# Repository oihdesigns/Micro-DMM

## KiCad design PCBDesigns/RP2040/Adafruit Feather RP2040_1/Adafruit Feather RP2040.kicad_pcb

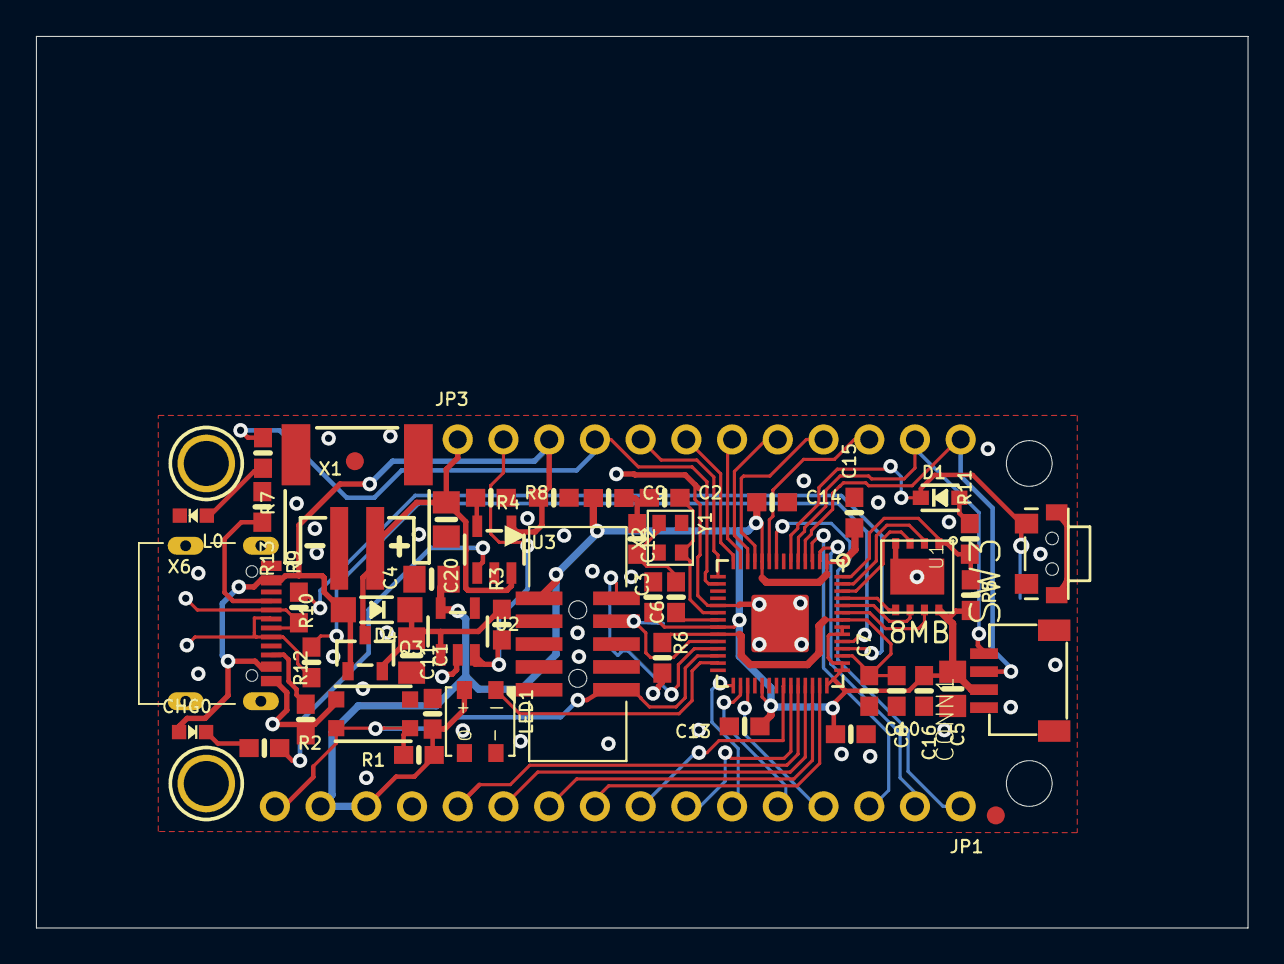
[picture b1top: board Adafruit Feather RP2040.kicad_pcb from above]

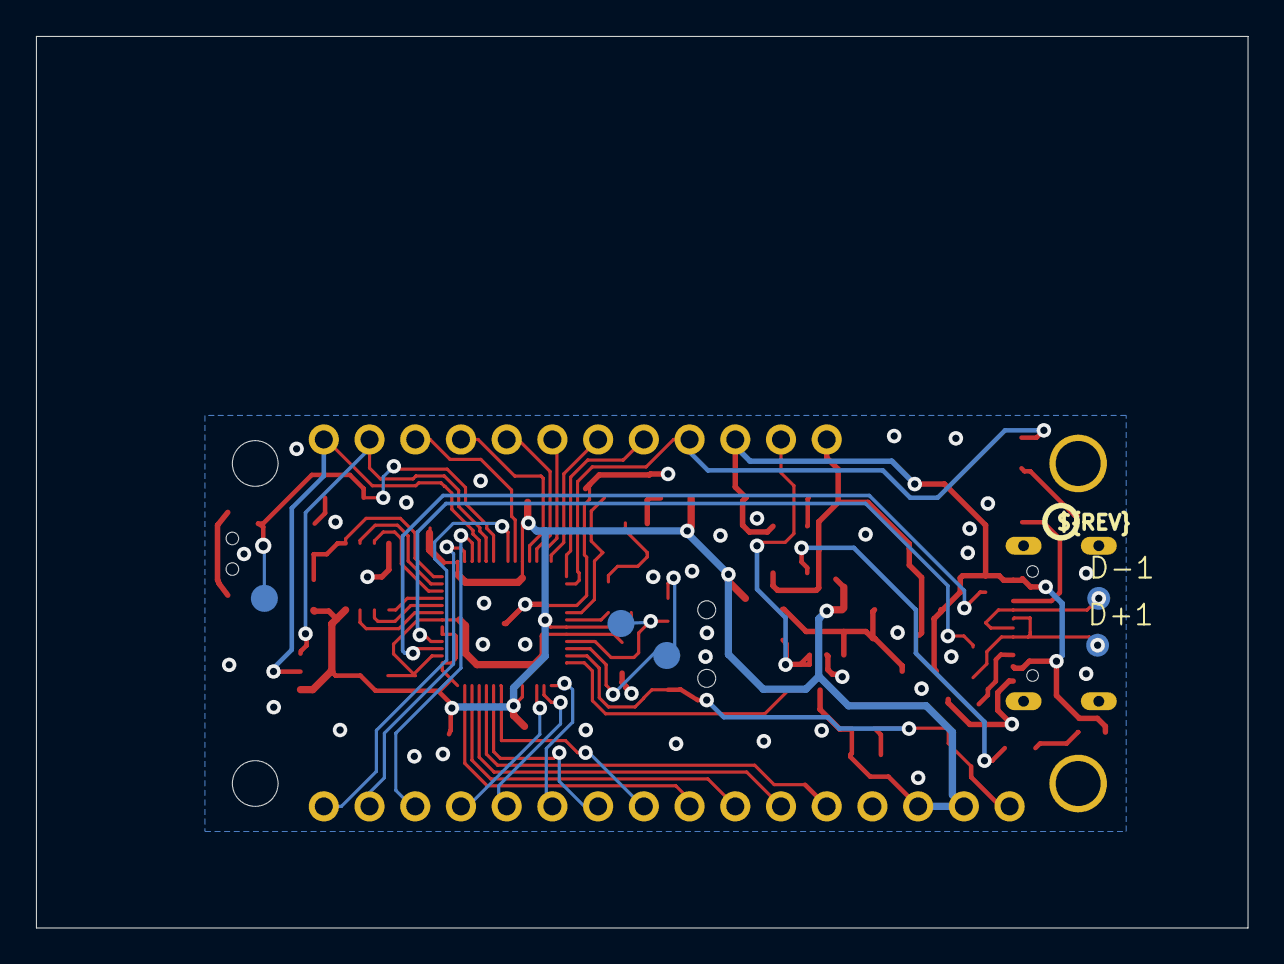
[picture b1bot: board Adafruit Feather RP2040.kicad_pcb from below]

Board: 2 copper layers, 67.3 x 49.5 mm, 63 parts (7 on the bottom side), 53 nets.

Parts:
C1, C4, C5, C20: 10uF; 0805-NO
C2, C3: 22pF; 0603-NO
C6, C7, C9, C11, C12, C13, C14, C15, C16: 0.1uF; 0603-NO
C8, C10: 1uF; 0603-NO
CHG0: ORANGE; CHIPLED_0603_NOOUTLINE
CONN1: STEMMA_I2C_QT; JST_SH4
D1: NSR0320; SOD-323_MINI
D4: MBR0540; SOD-123
D+1: TPB1,27; B1,27_385
D-1: TPB1,27; B1,27_385
IC1: RP2040_QFN56; QFN56_7MM_REDUCEDEPAD
JP1: 1X16_ROUND
JP3: 1X12_ROUND
L0: RED; CHIPLED_0603_NOOUTLINE
LED1: WS2812B3535; LED3535
Q3: DMG3415; SOT23-R
R1, R2, R3, R4, R5, R7: 10K; 0603-NO
R6, R11: 1K; 0603-NO
R8, R12, R13: 5.1K; 0603-NO
R9, R10: 27; 0603-NO
SW1: KMR2; BTN_KMR2_4.6X2.8
SW3: Mini RA Switch; SPST_TACTILE_RA_2_4_3.5MM
TP1, TP2, TP3: TESTPOINT_ROUND_1.5MM_NO
U1: W25Q64JVSSIQ; USON8_4X4
U2: RT9080/AP2112-3.3; SOT23-5
U3: MCP73831T-2ACI/OT; SOT23-5
U$1: RP2040_BOT
U$13: PCBFEAT-REV-040
U$31, U$32: MOUNTINGHOLE2.5; MOUNTINGHOLE_2.5_PLATED
U$34, U$35: FIDUCIAL_1MM
U$43: RP2040_TOP
UNK_HOLE_0: dummyfp0
UNK_HOLE_1: dummyfp1
X1: JSTPH; JSTPH2_BATT
X2: 2x5 SWD; 2X05_1.27MM_BOX_NOCREAM
X6: USB Type C; USB_C_CUSB31-CFM2AX-01-X
Y1: 12MHz/12pF; CRYSTAL_2.5X2

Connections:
1.2V: C6.2, C7.2, C8.1, IC1.23, IC1.45, IC1.50
+3V3: C4.1, C5.1, C9.1, C10.1, C11.1, C12.1, C13.1, C14.1, C15.1, C16.1, CONN1.2, IC1.1, IC1.10, IC1.22, IC1.33, IC1.42, IC1.43, IC1.44, IC1.48, IC1.49, JP1.14, JP1.15, LED1.2, R1.1, R5.2, U1.8, U2.5, X2.1
A0: IC1.38, JP1.12
A1: IC1.39, JP1.11
A2: IC1.40, JP1.10
A3: IC1.41, JP1.9
CC1: R13.2, X6.A5
CC2: R12.2, X6.B5
D4: IC1.8, JP1.1
D5: IC1.9, JP3.10
D6: IC1.11, JP3.9
D9: IC1.12, JP3.8
D10: IC1.13, JP3.7
D11: IC1.14, JP3.6
D12: IC1.15, JP3.5
D13: IC1.16, JP3.4, R7.1
D24: IC1.36, JP1.8
D25: IC1.37, JP1.7
D+: IC1.47, R10.2
D-: IC1.46, R9.2
EN: JP3.2, R3.1, U2.3
GND: C1.2, C2.1, C3.1, C4.2, C5.2, C6.1, C7.1, C8.2, C9.2, C10.2, C11.2, C12.2, C13.2, C14.2, C15.2, C16.2, C20.2, CONN1.1, CONN1.MT1, CONN1.MT2, IC1.19, IC1.P$1, JP1.13, L0.C, LED1.4, R4.1, R8.2, R12.1, R13.1, SW1.B, SW1.B', SW3.1, SW3.MT1, SW3.MT2, U1.4, U1.PAD, U2.2, U3.2, X1.1, X1.NC1, X1.NC2, X2.3, X2.5, X2.7, X2.9, X6.A1B12, X6.B1A12
MISO: IC1.31, JP1.4
MOSI: IC1.30, JP1.5
unnamed: CHG0.C, R2.1
unnamed: L0.A, R7.2
unnamed: R2.2, U3.1
unnamed: R8.1, U3.5
unnamed: C2.2, IC1.20, Y1.3
unnamed: C3.2, R6.1, Y1.1
unnamed: IC1.21, R6.2
unnamed: D1.A, R11.2
NEOPIX: IC1.27, LED1.1
QSPI_CS: IC1.56, R5.1, R11.1, U1.1
QSPI_DATA[0]: IC1.53, U1.5
QSPI_DATA[1]: IC1.55, U1.2
QSPI_DATA[2]: IC1.54, U1.3
QSPI_DATA[3]: IC1.51, U1.7
QSPI_SCK: IC1.52, U1.6
RX: IC1.3, JP1.3
SCK: IC1.29, JP1.6
SCL: CONN1.4, IC1.5, JP3.11
SDA: CONN1.3, IC1.4, JP3.12
SWCLK: IC1.24, TP2.P$1, X2.4
SWDIO: IC1.25, TP1.P$1, X2.2
TX: IC1.2, JP1.2
USBBOOT: D1.C, IC1.6, SW3.2, TP3.P$1
USB_D+: D+1.TP, R10.1, X6.A6, X6.B6
USB_D-: D-1.TP, R9.1, X6.A7, X6.B7
VBAT: C20.1, JP3.1, Q3.3, U3.3, X1.2
VBUS: CHG0.A, D4.A, JP3.3, Q3.1, R4.2, U3.4, X6.A4B9, X6.B4A9
VHI: C1.1, D4.C, Q3.2, R3.2, U2.1
~RESET: IC1.26, JP1.16, R1.2, SW1.A, SW1.A', X2.10

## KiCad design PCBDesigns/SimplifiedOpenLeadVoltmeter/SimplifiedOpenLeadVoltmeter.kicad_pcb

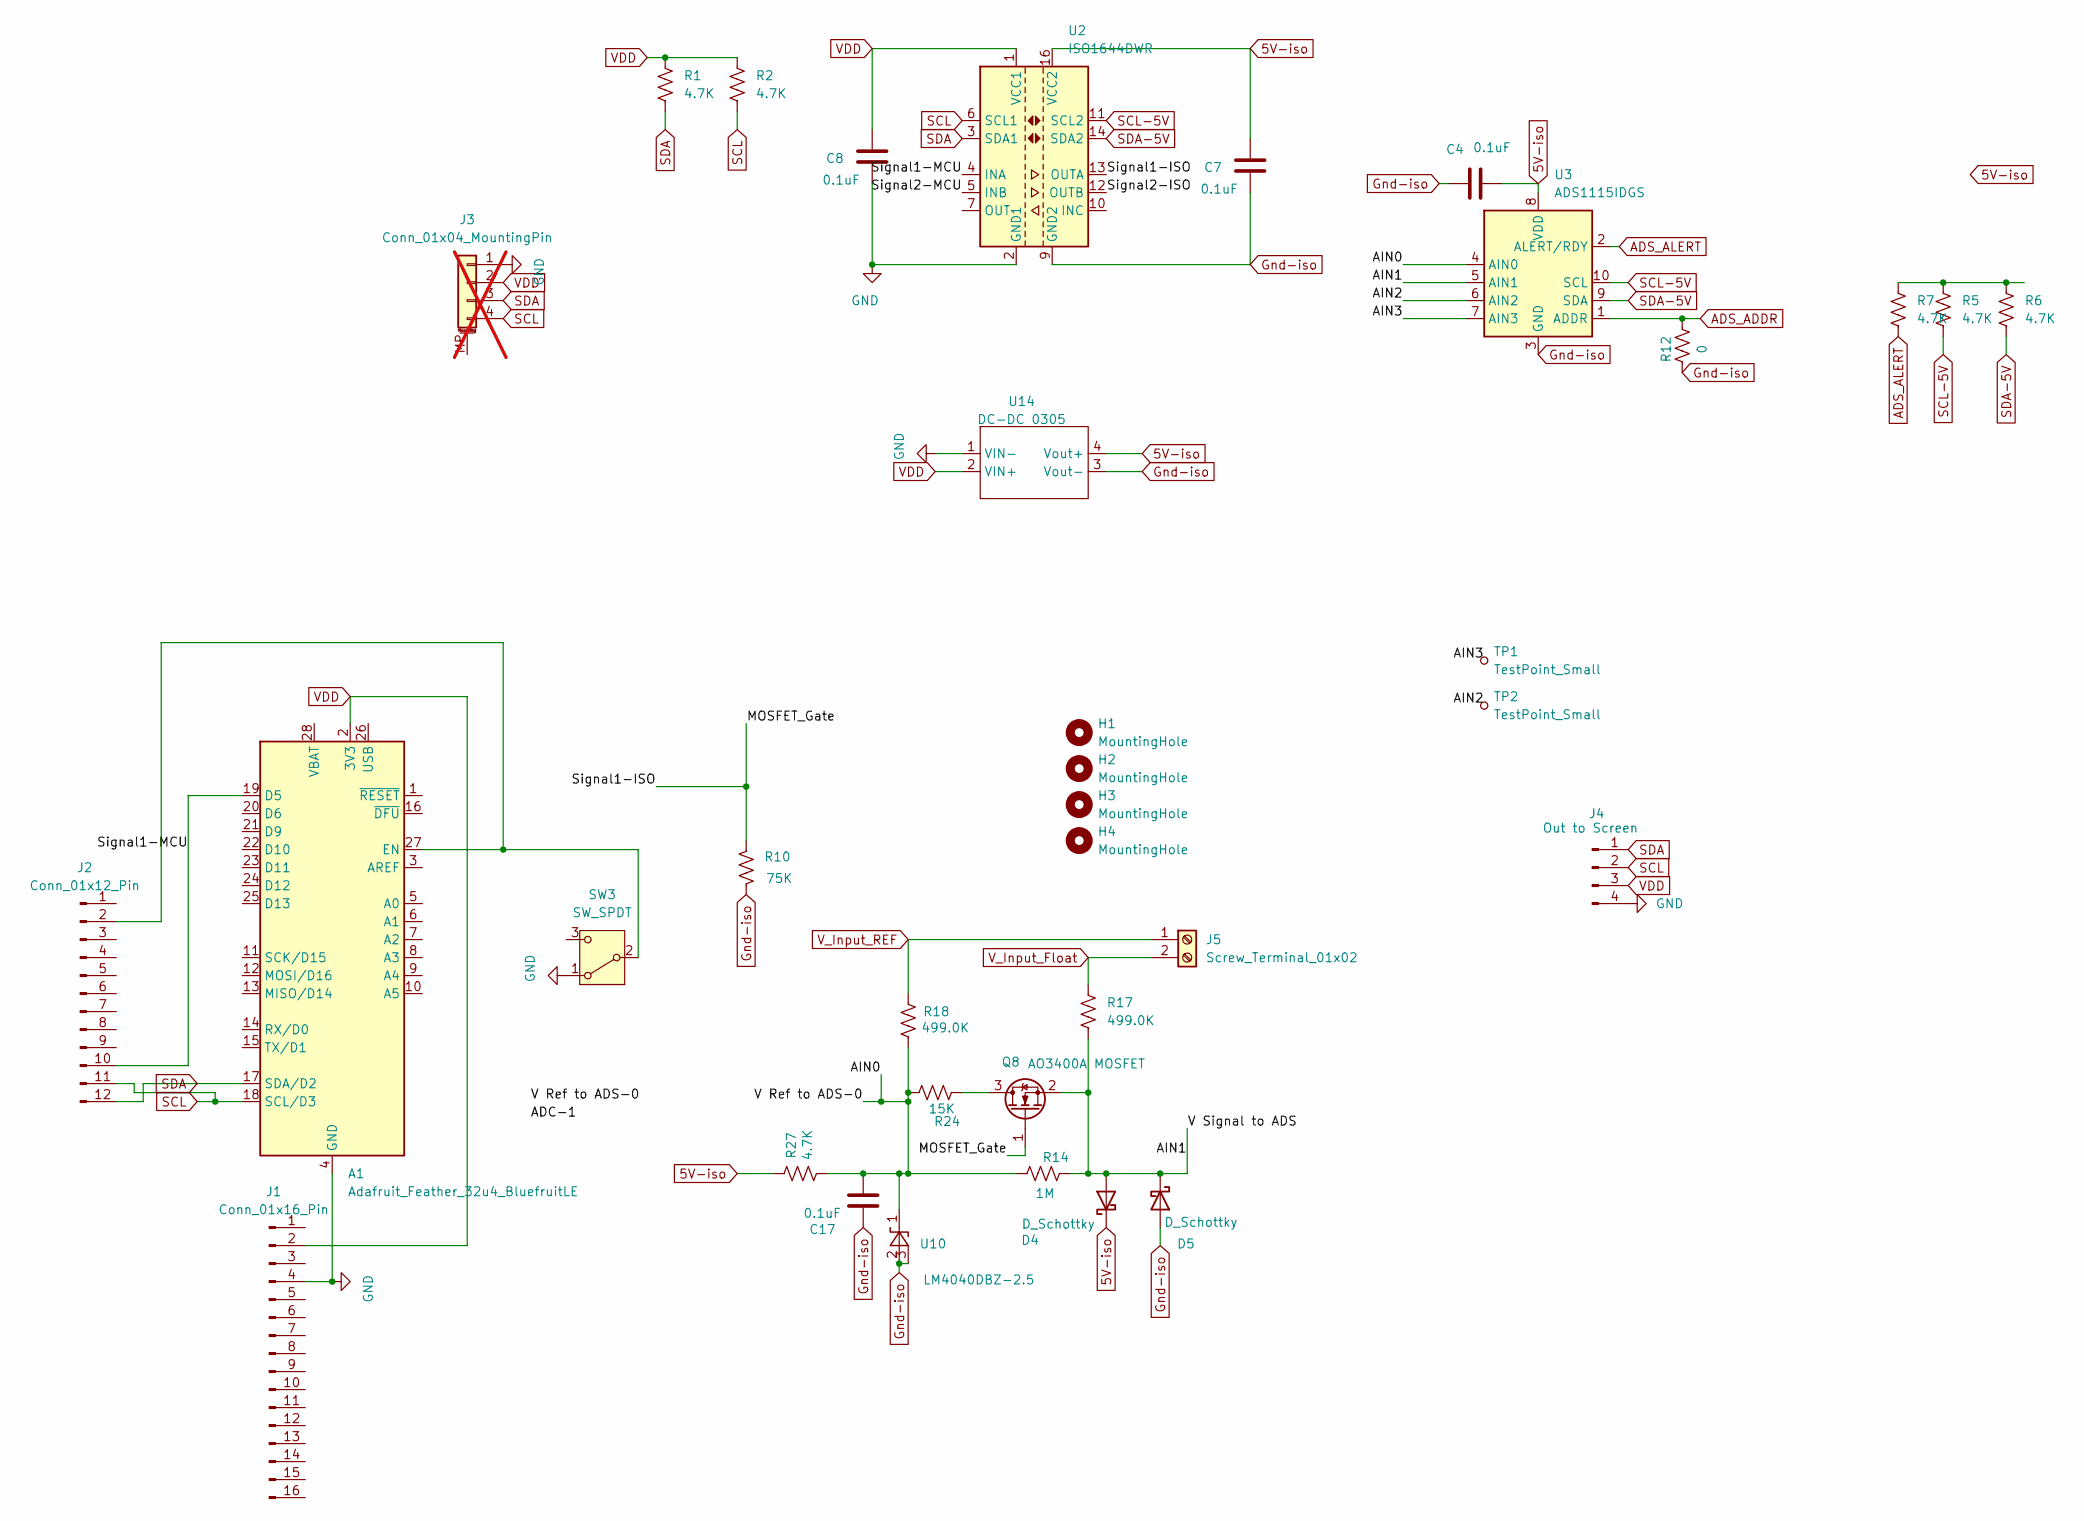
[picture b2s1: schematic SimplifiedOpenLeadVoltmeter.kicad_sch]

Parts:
A1: Adafruit_Feather_32u4_BluefruitLE; Adafruit_Feather_WithMountingHoles
C4, C7, C8, C17: 0.1uF; C_0603_1608Metric_Pad1.08x0.95mm_HandSolder
D4, D5: D_Schottky; D_SOD-123
H1, H2, H3: MountingHole; MountingHole_2.2mm_M2_Pad
H4: MountingHole; MountingHole_2.2mm_M2_ISO14580
J1: Conn_01x16_Pin; PinSocket_1x16_P2.54mm_Vertical
J2: Conn_01x12_Pin; PinSocket_1x12_P2.54mm_Vertical
J3: Conn_01x04_MountingPin; JST_SH_SM04B-SRSS-TB_1x04-1MP_P1.00mm_Horizontal; not fitted
J4: Out to Screen; PinSocket_1x04_P2.54mm_Vertical
J5: Screw_Terminal_01x02; TerminalBlock_CUI_TB007-508-02_1x02_P5.08mm_Horizontal
Q8: AO3400A MOSFET; SOT-23
R1, R2, R5, R6, R7, R27: 4.7K; R_0603_1608Metric_Pad0.98x0.95mm_HandSolder
R10: 75K; R_0603_1608Metric_Pad0.98x0.95mm_HandSolder
R12: 0; R_0805_2012Metric_Pad1.20x1.40mm_HandSolder
R14: 1M; R_0805_2012Metric_Pad1.20x1.40mm_HandSolder
R17, R18: 499.0K; R_0805_2012Metric_Pad1.20x1.40mm_HandSolder
R24: 15K; R_0805_2012Metric_Pad1.20x1.40mm_HandSolder
SW3: SW_SPDT; SW_Slide_SPDT_Angled_CK_OS102011MA1Q
TP1, TP2: TestPoint_Small; TestPoint_Pad_D1.0mm
U2: ISO1644DWR; SOIC-16W_7.5x10.3mm_P1.27mm
U3: ADS1115IDGS; TSSOP-10_3x3mm_P0.5mm
U10: LM4040DBZ-2.5; SOT-23
U14: DC-DC 0305; XP SCT01F03S05

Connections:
5V-iso: C4.2, C7.1, D4.1 (K), R27.1, U2.16 (VCC2), U3.8 (VDD), U14.4 (Vout+)
/AIN0: C17.2, R14.1, R18.2, R24.2, R27.2, U3.4 (AIN0), U10.1 (K)
/AIN1: D4.2 (A), D5.1 (K), Q8.2 (S), R14.2, R17.2, U3.5 (AIN1)
/AIN2: TP2.1 (1_1), U3.6 (AIN2)
/AIN3: TP1.1 (1_1), U3.7 (AIN3)
/MOSFET_Gate: Q8.1 (G), R10.2, U2.13 (OUTA)
/Signal1-MCU: A1.19 (D5), J2.10, U2.4 (INA)
/Signal2-ISO: U2.12 (OUTB)
/Signal2-MCU: U2.5 (INB)
ADS_ADDR: R12.1, U3.1 (ADDR)
ADS_ALERT: R7.2, U3.2 (ALERT/RDY)
GND: A1.4 (GND), C8.2, J1.4, J3.1, J4.4, SW3.1 (A), U2.2 (GND1), U2.8 (GND1), U14.1 (VIN-)
Gnd-iso: C4.1, C7.2, C17.1, D5.2 (A), R10.1, R12.2, U2.9 (GND2), U2.15 (GND2), U3.3 (GND), U10.2 (A), U10.3 (nc_(gnd)), U14.3 (Vout-)
unnamed: A1.27 (EN), J2.2, SW3.2 (B)
unnamed: Q8.3 (D), R24.1
unnamed: R5.1, R6.1, R7.1
SCL: A1.18 (SCL/D3), J2.11, J3.4, J4.2, R2.2, U2.6 (SCL1)
SCL-5V: R5.2, U2.11 (SCL2), U3.10 (SCL)
SDA: A1.17 (SDA/D2), J2.12, J3.3, J4.1, R1.2, U2.3 (SDA1)
SDA-5V: R6.2, U2.14 (SDA2), U3.9 (SDA)
VDD: A1.2 (3V3), C8.1, J1.2, J3.2, J4.3, R1.1, R2.1, U2.1 (VCC1), U14.2 (VIN+)
V_Input_Float: J5.2, R17.1
V_Input_REF: J5.1, R18.1

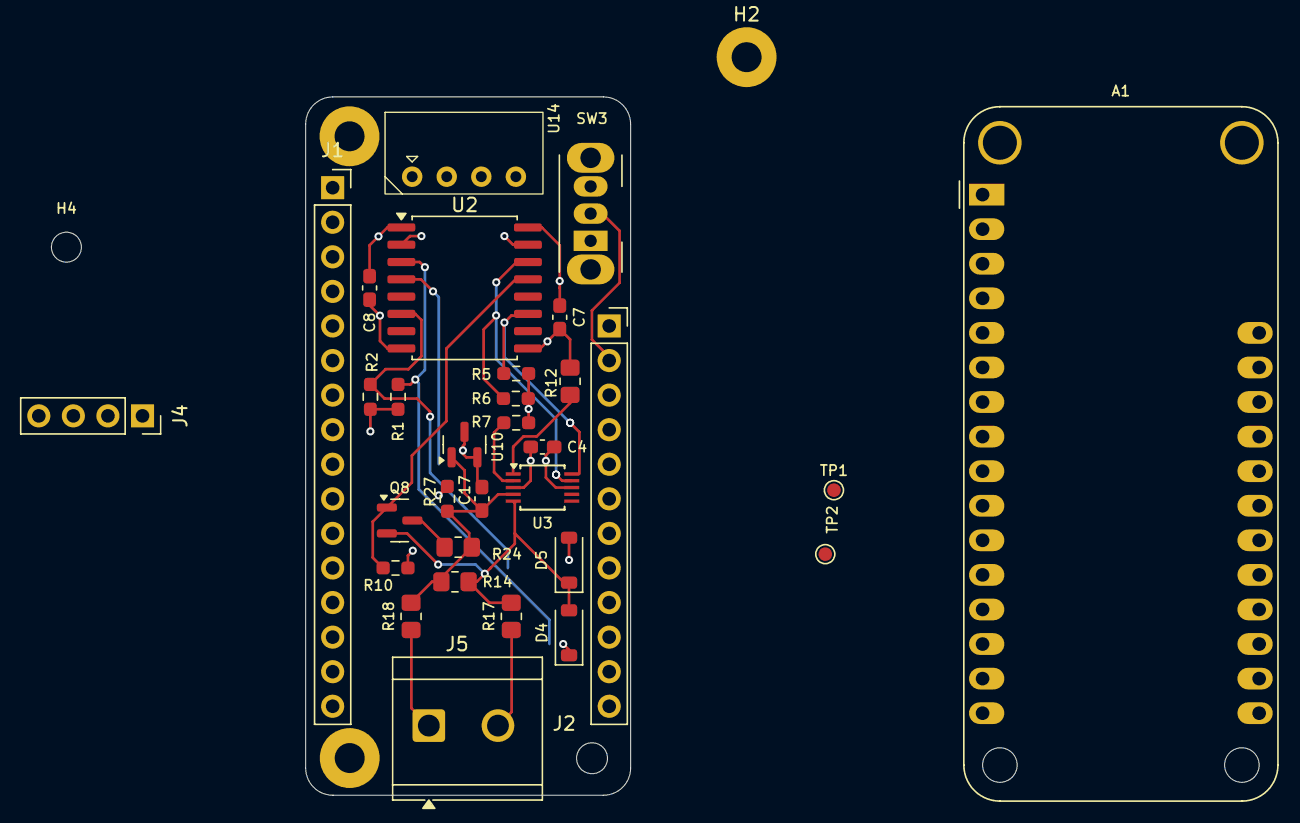
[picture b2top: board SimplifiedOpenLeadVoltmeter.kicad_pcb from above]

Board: 4 copper layers, 23.9 x 51.3 mm, 35 parts (0 on the bottom side), 21 nets.

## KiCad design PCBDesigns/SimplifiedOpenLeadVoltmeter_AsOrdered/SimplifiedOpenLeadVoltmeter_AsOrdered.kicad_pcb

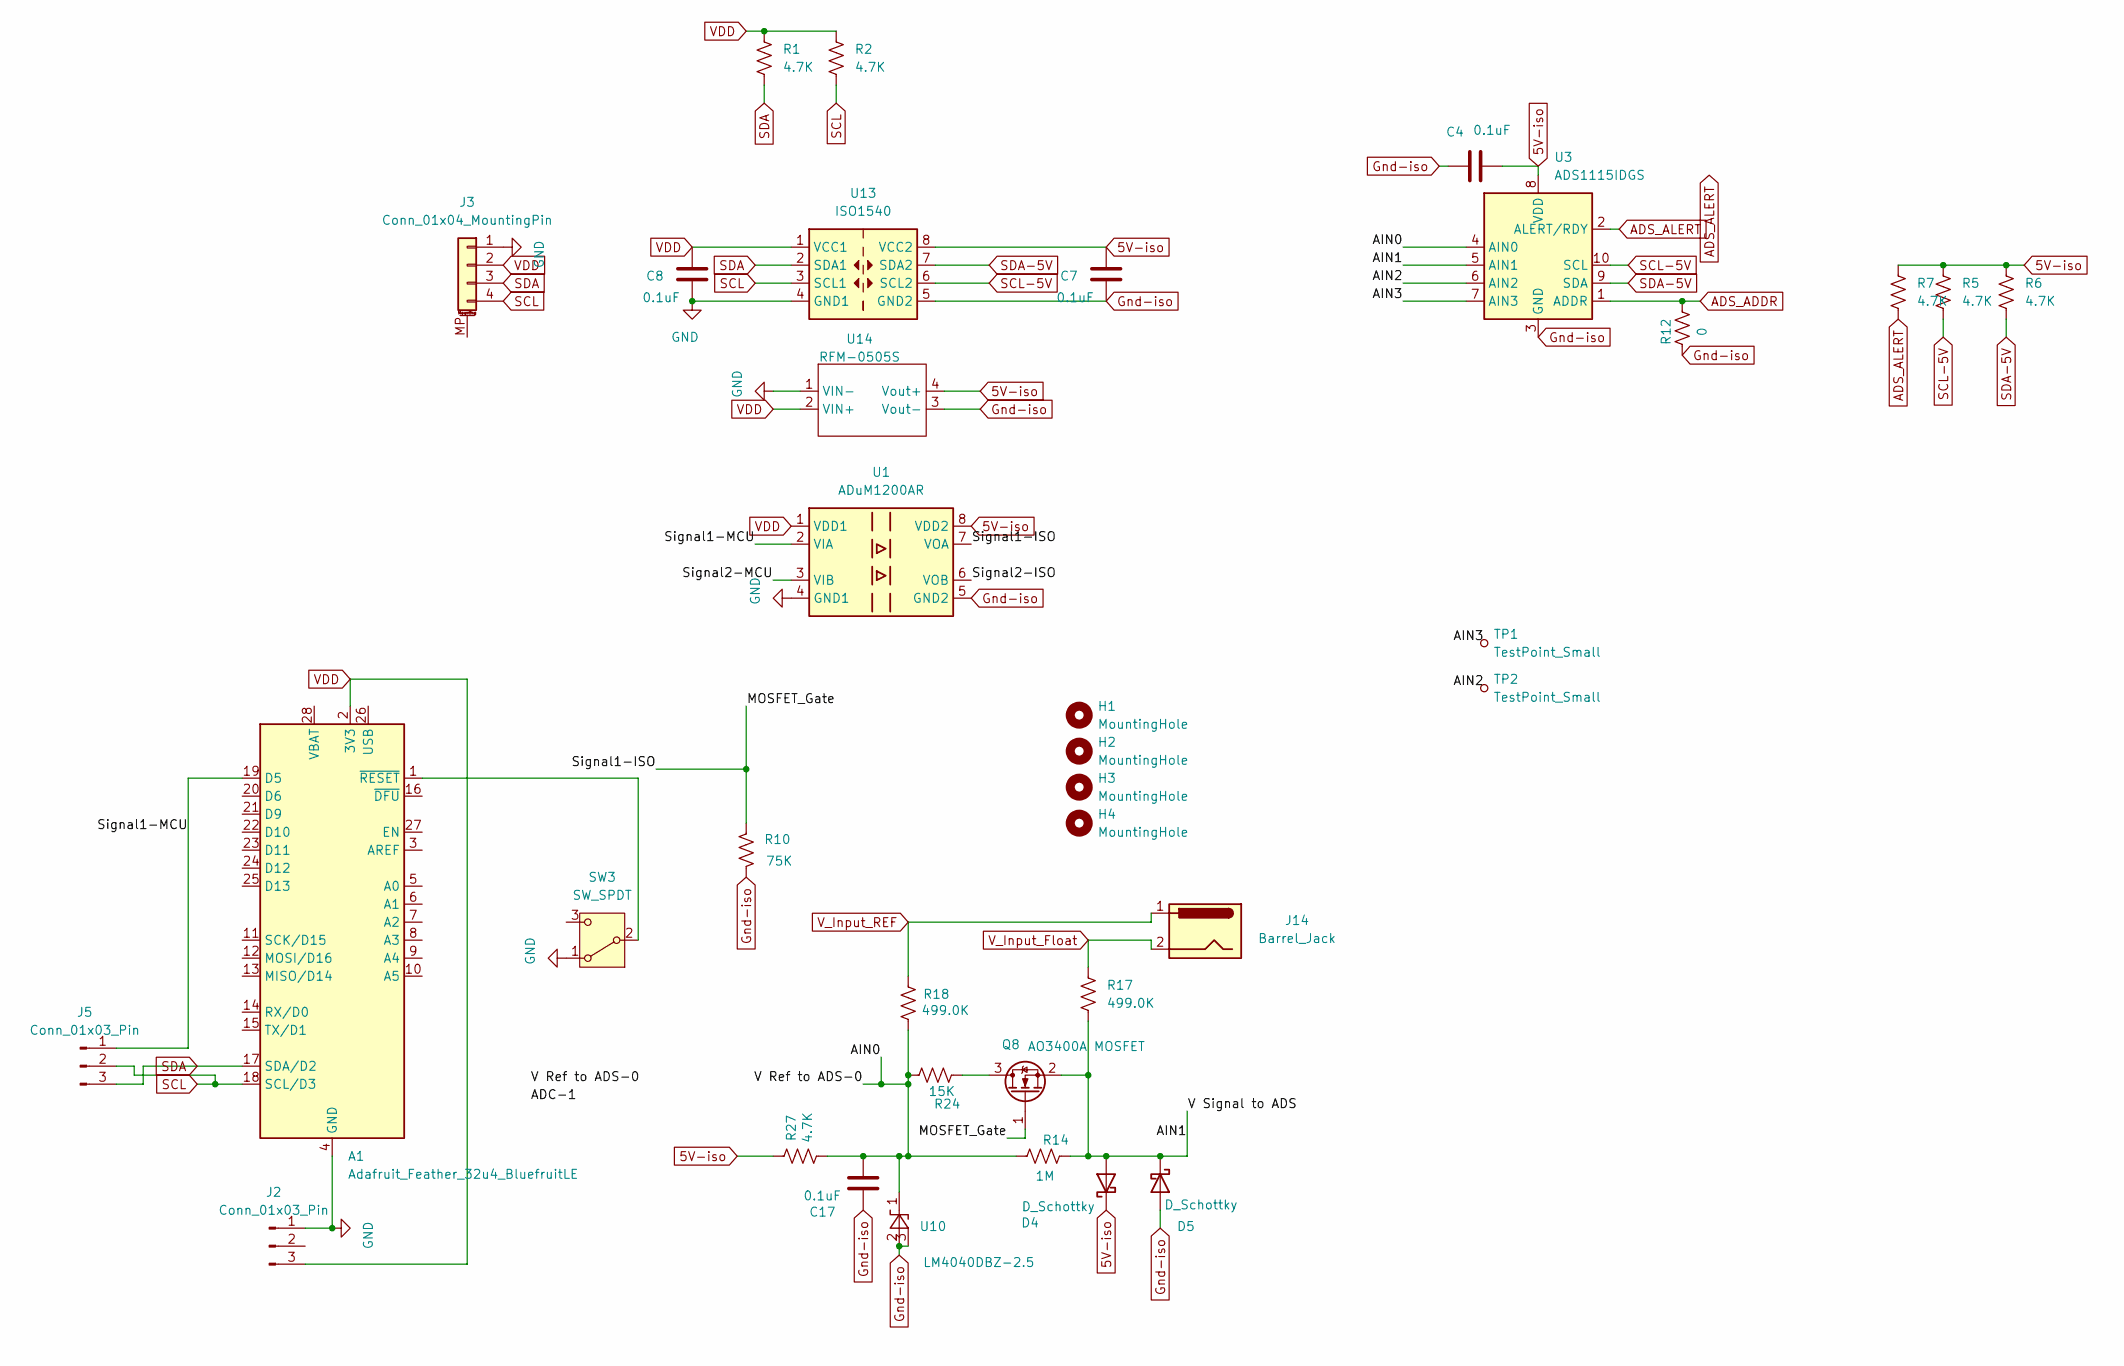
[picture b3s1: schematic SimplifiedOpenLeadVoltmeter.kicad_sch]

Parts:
A1: Adafruit_Feather_32u4_BluefruitLE; Adafruit_Feather_WithMountingHoles
C4, C7, C8, C17: 0.1uF; C_0805_2012Metric_Pad1.18x1.45mm_HandSolder
D4, D5: D_Schottky; D_SOD-123
H1, H2, H3: MountingHole; MountingHole_2.2mm_M2_Pad
H4: MountingHole; MountingHole_2.2mm_M2_ISO14580
J2, J5: Conn_01x03_Pin; PinHeader_1x03_P2.54mm_Vertical
J3: Conn_01x04_MountingPin; JST_SH_SM04B-SRSS-TB_1x04-1MP_P1.00mm_Horizontal
J14: Barrel_Jack; BarrelJack_Horizontal
Q8: AO3400A MOSFET; SOT-23
R1, R2, R5, R6, R7, R27: 4.7K; R_0805_2012Metric_Pad1.20x1.40mm_HandSolder
R10: 75K; R_0805_2012Metric_Pad1.20x1.40mm_HandSolder
R12: 0; R_0805_2012Metric_Pad1.20x1.40mm_HandSolder
R14: 1M; R_0805_2012Metric_Pad1.20x1.40mm_HandSolder
R17, R18: 499.0K; R_0805_2012Metric_Pad1.20x1.40mm_HandSolder
R24: 15K; R_0805_2012Metric_Pad1.20x1.40mm_HandSolder
SW3: SW_SPDT; SW_Slide_SPDT_Angled_CK_OS102011MA1Q
TP1, TP2: TestPoint_Small; TestPoint_Pad_D1.0mm
U1: ADuM1200AR; SOIC-8_3.9x4.9mm_P1.27mm
U3: ADS1115IDGS; TSSOP-10_3x3mm_P0.5mm
U10: LM4040DBZ-2.5; SOT-23
U13: ISO1540; SOIC-8_3.9x4.9mm_P1.27mm
U14: RFM-0505S; XP SCT01F03S05

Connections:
5V-iso: C4.2, C7.1, D4.1 (K), R5.1, R6.1, R7.1, R27.1, U1.8 (VDD2), U3.8 (VDD), U13.8 (VCC2), U14.4 (Vout+)
/AIN0: C17.2, R14.1, R18.2, R24.2, R27.2, U3.4 (AIN0), U10.1 (K)
/AIN1: D4.2 (A), D5.1 (K), Q8.2 (S), R14.2, R17.2, U3.5 (AIN1)
/AIN2: TP2.1, U3.6 (AIN2)
/AIN3: TP1.1, U3.7 (AIN3)
/MOSFET_Gate: Q8.1 (G), R10.2, U1.7 (VOA)
/Signal1-MCU: A1.19 (D5), J5.1, U1.2 (VIA)
/Signal2-ISO: U1.6 (VOB)
/Signal2-MCU: U1.3 (VIB)
ADS_ADDR: R12.1, U3.1 (ADDR)
ADS_ALERT: R7.2, U3.2 (ALERT/RDY)
GND: A1.4 (GND), C8.2, J2.1, J3.1, SW3.1 (A), U1.4 (GND1), U13.4 (GND1), U14.1 (VIN-)
Gnd-iso: C4.1, C7.2, C17.1, D5.2 (A), R10.1, R12.2, U1.5 (GND2), U3.3 (GND), U10.2 (A), U10.3 (nc_(gnd)), U13.5 (GND2), U14.3 (Vout-)
unnamed: A1.1 (~RESET), SW3.2 (B)
unnamed: Q8.3 (D), R24.1
SCL: A1.18 (SCL/D3), J3.4, J5.2, R2.2, U13.3 (SCL1)
SCL-5V: R5.2, U3.10 (SCL), U13.6 (SCL2)
SDA: A1.17 (SDA/D2), J3.3, J5.3, R1.2, U13.2 (SDA1)
SDA-5V: R6.2, U3.9 (SDA), U13.7 (SDA2)
VDD: A1.2 (3V3), C8.1, J2.3, J3.2, R1.1, R2.1, U1.1 (VDD1), U13.1 (VCC1), U14.2 (VIN+)
V_Input_Float: J14.2, R17.1
V_Input_REF: J14.1, R18.1

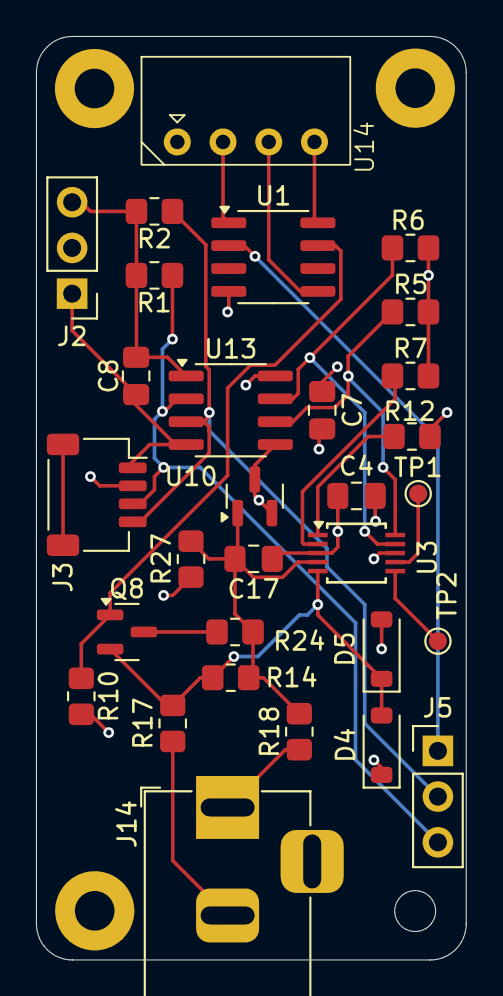
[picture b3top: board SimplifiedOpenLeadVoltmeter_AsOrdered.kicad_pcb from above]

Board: 4 copper layers, 23.9 x 51.3 mm, 33 parts (0 on the bottom side), 19 nets.

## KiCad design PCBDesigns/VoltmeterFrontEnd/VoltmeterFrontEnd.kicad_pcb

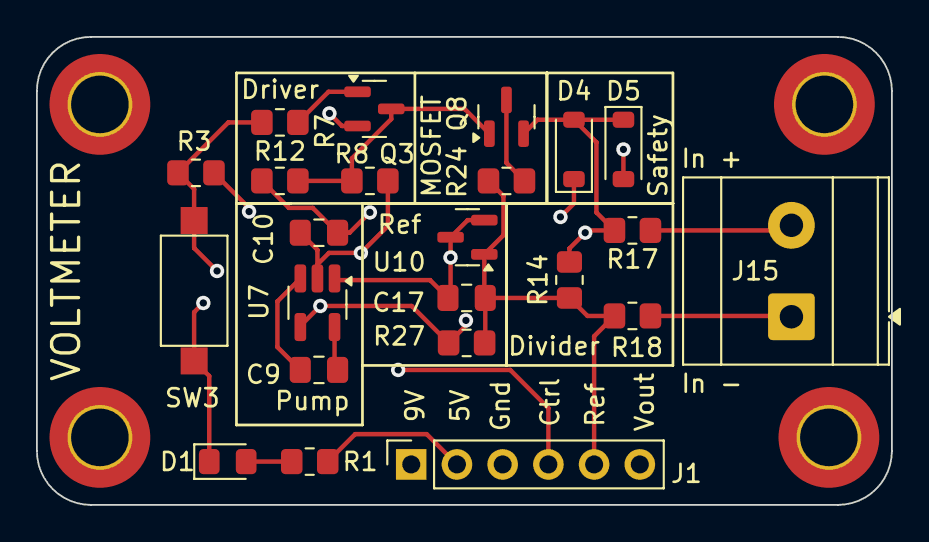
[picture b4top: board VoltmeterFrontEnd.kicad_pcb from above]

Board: 4 copper layers, 47.5 x 26.0 mm, 27 parts (0 on the bottom side), 14 nets.

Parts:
C9, C10: 4.7uF; C_0805_2012Metric_Pad1.18x1.45mm_HandSolder
C17: 0.1uF; C_0805_2012Metric_Pad1.18x1.45mm_HandSolder
D1: LED; LED_0805_2012Metric_Pad1.15x1.40mm_HandSolder
D4, D5: D_Schottky; D_SOD-123
H1, H2, H3, H4: MountingHole; MountingHole_3.2mm_M3_DIN965_Pad_TopBottom
J1: Voltmeter; PinSocket_1x06_P2.54mm_Vertical
J15: Barrel_Jack; TerminalBlock_Phoenix_MKDS-3-2-5.08_1x02_P5.08mm_Horizontal
Q3: MMBT3904; SOT-23
Q8: AO3400A MOSFET; SOT-23
R1: 1K; R_0805_2012Metric_Pad1.20x1.40mm_HandSolder
R3, R8: 10K; R_0805_2012Metric_Pad1.20x1.40mm_HandSolder
R7: 22K; R_0805_2012Metric_Pad1.20x1.40mm_HandSolder
R12: 100K; R_0805_2012Metric_Pad1.20x1.40mm_HandSolder
R14: 15.0K; R_0805_2012Metric_Pad1.20x1.40mm_HandSolder
R17, R18: 499.0K; R_0805_2012Metric_Pad1.20x1.40mm_HandSolder
R24: 1.0M; R_0805_2012Metric_Pad1.20x1.40mm_HandSolder
R27: 4.7K; R_0805_2012Metric_Pad1.20x1.40mm_HandSolder
SW3: SW_Push; SW_SPST_CK_RS282G05A3
U7: MAX1683; SOT-23-5_HandSoldering
U10: LM4040DBZ-2.5; SOT-23

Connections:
+9V: C10.2, J1.1, R8.2, U7.2 (Out)
/ADC-1: D4.2 (A), D5.1 (K), J1.6, Q8.2 (S), R14.2, R17.2
/MOSFET_Gate: Q3.3 (C), Q8.1 (G), R8.1, R12.2
/V Ref to ADS-0: C17.2, J1.5, R14.1, R18.2, R24.2, R27.2, U10.1 (K)
GND: C10.1, C17.1, D1.1 (K), D5.2 (A), J1.3, Q3.2 (E), R12.1, SW3.2, U7.1 (Gnd), U10.2 (A), U10.3 (nc_(gnd))
MOSFET_Ctrl: J1.4, R3.2, R7.1, SW3.1
unnamed: D1.2 (A), R1.2
unnamed: Q3.1 (B), R7.2
unnamed: Q8.3 (D), R24.1
unnamed: C9.2, U7.5 (C1+)
unnamed: C9.1, U7.3 (C1-)
VDD: D4.1 (K), J1.2, R1.1, R3.1, R27.1, U7.4 (In)
V_Input_Float: J15.2, R17.1
V_Input_REF: J15.1, R18.1

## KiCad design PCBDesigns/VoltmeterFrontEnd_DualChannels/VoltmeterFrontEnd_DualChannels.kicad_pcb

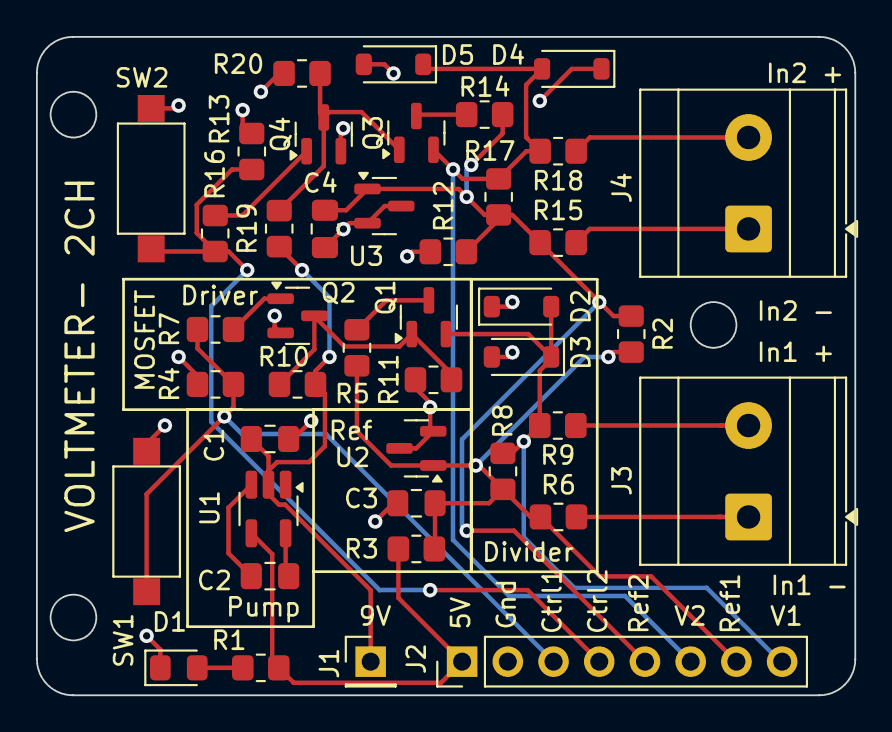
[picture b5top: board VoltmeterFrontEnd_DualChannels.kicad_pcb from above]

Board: 4 copper layers, 45.5 x 36.6 mm, 42 parts (0 on the bottom side), 22 nets.

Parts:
C1, C2: 4.7uF; C_0805_2012Metric_Pad1.18x1.45mm_HandSolder
C3, C4: 0.1uF; C_0805_2012Metric_Pad1.18x1.45mm_HandSolder
D1: LED; LED_0805_2012Metric_Pad1.15x1.40mm_HandSolder
D2, D3, D4, D5: D_Schottky; D_SOD-123
J1: Conn_01x01_Pin; PinHeader_1x01_P2.54mm_Vertical
J2: Conn_01x08_Pin; PinHeader_1x08_P2.54mm_Vertical
J3, J4: Barrel_Jack; TerminalBlock_Phoenix_MKDS-3-2-5.08_1x02_P5.08mm_Horizontal
Q1, Q3: AO3400A MOSFET; SOT-23
Q2, Q4: MMBT3904; SOT-23
R1: 1K; R_0805_2012Metric_Pad1.20x1.40mm_HandSolder
R2: 0; R_0805_2012Metric_Pad1.20x1.40mm_HandSolder
R3, R12: 4.7K; R_0805_2012Metric_Pad1.20x1.40mm_HandSolder
R4, R10, R13, R19: 10K; R_0805_2012Metric_Pad1.20x1.40mm_HandSolder
R5, R14: 15K; R_0805_2012Metric_Pad1.20x1.40mm_HandSolder
R6, R9, R15, R18: 499.0K; R_0805_2012Metric_Pad1.20x1.40mm_HandSolder
R7, R16: 22K; R_0805_2012Metric_Pad1.20x1.40mm_HandSolder
R8, R17: 1M; R_0805_2012Metric_Pad1.20x1.40mm_HandSolder
R11, R20: 100K; R_0805_2012Metric_Pad1.20x1.40mm_HandSolder
SW1, SW2: SW_Push; SW_SPST_CK_RS282G05A3
U1: MAX1683; SOT-23-5_HandSoldering
U2, U3: LM4040DBZ-2.5; SOT-23

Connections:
+9V: C1.2, J1.1, R10.2, R19.2, U1.2 (Out)
/ADC-1: C3.2, J2.7, R2.1, R3.2, R5.2, R6.2, R8.1, U2.1 (K)
/ADC-3: C4.2, J2.5, R2.2, R12.2, R14.2, R15.2, R17.1, U3.1 (K)
/V Ref to ADS-0: D2.2 (A), D3.1 (K), J2.8, Q1.2 (S), R8.2, R9.2
/V Ref to ADS-2: D4.2 (A), D5.1 (K), J2.6, Q3.2 (S), R17.2, R18.2
/Volt Conditioner1/V_Input_Float: J4.2, R18.1
/Volt Conditioner1/V_Input_Ref: J4.1, R15.1
/Volt Conditioner/V_Input_Float: J3.2, R9.1
/Volt Conditioner/V_Input_Ref: J3.1, R6.1
GND: C1.1, C3.1, C4.1, D1.1 (K), D3.2 (A), D5.2 (A), J2.2, Q2.2 (E), Q4.2 (E), R11.1, R20.1, SW1.2, SW2.2, U1.1 (Gnd), U2.2 (A), U2.3 (nc_(gnd)), U3.2 (A), U3.3 (nc_(gnd))
MOSFET_Ctrl: J2.3, R4.2, R7.1, SW1.1
MOSFET_Ctrl2: J2.4, R13.2, R16.1, SW2.1
unnamed: D1.2 (A), R1.2
unnamed: Q1.3 (D), R5.1
unnamed: Q1.1 (G), Q2.3 (C), R10.1, R11.2
unnamed: Q2.1 (B), R7.2
unnamed: Q3.3 (D), R14.1
unnamed: Q3.1 (G), Q4.3 (C), R19.1, R20.2
unnamed: Q4.1 (B), R16.2
unnamed: C2.2, U1.5 (C1+)
unnamed: C2.1, U1.3 (C1-)
VDD: D2.1 (K), D4.1 (K), J2.1, R1.1, R3.1, R4.1, R12.1, R13.1, U1.4 (In)

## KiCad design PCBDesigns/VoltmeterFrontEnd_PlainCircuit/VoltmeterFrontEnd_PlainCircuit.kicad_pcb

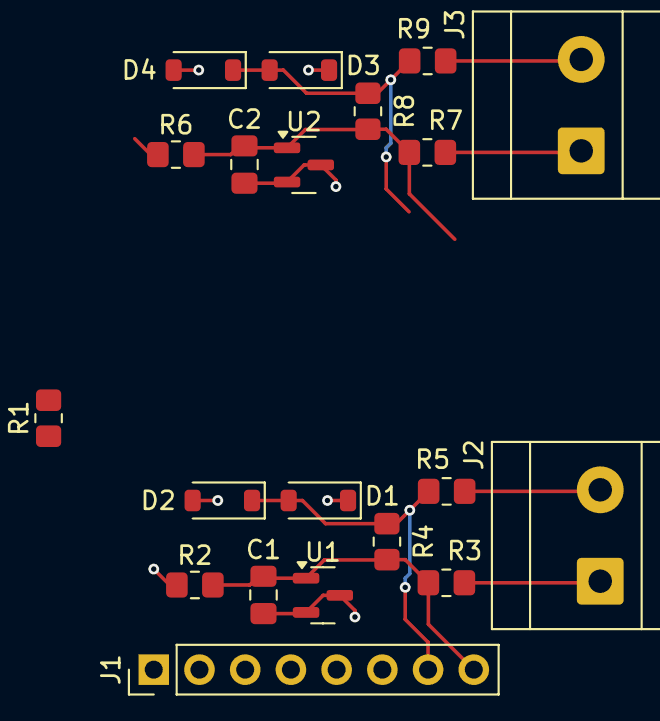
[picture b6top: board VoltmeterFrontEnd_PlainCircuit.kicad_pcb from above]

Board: 4 copper layers, 20 parts (0 on the bottom side), 10 nets.

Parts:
C1, C2: 0.1uF; C_0805_2012Metric_Pad1.18x1.45mm_HandSolder
D1, D2, D3, D4: D_Schottky; D_SOD-123
J1: Conn_01x08_Pin; PinHeader_1x08_P2.54mm_Vertical
J2, J3: Barrel_Jack; TerminalBlock_Phoenix_MKDS-3-2-5.08_1x02_P5.08mm_Horizontal
R1: 0; R_0805_2012Metric_Pad1.20x1.40mm_HandSolder
R2, R6: 4.7K; R_0805_2012Metric_Pad1.20x1.40mm_HandSolder
R3, R5, R7, R9: 499.0K; R_0805_2012Metric_Pad1.20x1.40mm_HandSolder
R4, R8: 15K; R_0805_2012Metric_Pad1.20x1.40mm_HandSolder
U1, U2: LM4040DBZ-2.5; SOT-23

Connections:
/ADC-1: D1.2 (A), D2.1 (K), J1.7, R4.2, R5.2
/ADC-3: D3.2 (A), D4.1 (K), J1.5, R8.2, R9.2
/V Ref to ADS-0: C1.2, J1.8, R1.2, R2.2, R3.2, R4.1, U1.1 (K)
/V Ref to ADS-2: C2.2, J1.6, R1.1, R6.2, R7.2, R8.1, U2.1 (K)
/VoltmeterPlain1/V_Input_Float: J3.2, R9.1
/VoltmeterPlain1/V_Input_Ref: J3.1, R7.1
/VoltmeterPlain/V_Input_Float: J2.2, R5.1
/VoltmeterPlain/V_Input_Ref: J2.1, R3.1
GND: C1.1, C2.1, D2.2 (A), D4.2 (A), J1.2, U1.2 (A), U1.3 (nc_(gnd)), U2.2 (A), U2.3 (nc_(gnd))
VDD: D1.1 (K), D3.1 (K), J1.1, R2.1, R6.1
